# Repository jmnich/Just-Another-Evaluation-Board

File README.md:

# STM32G474QE evaluation board

Just Another Evaluation Board with as few features as possible.

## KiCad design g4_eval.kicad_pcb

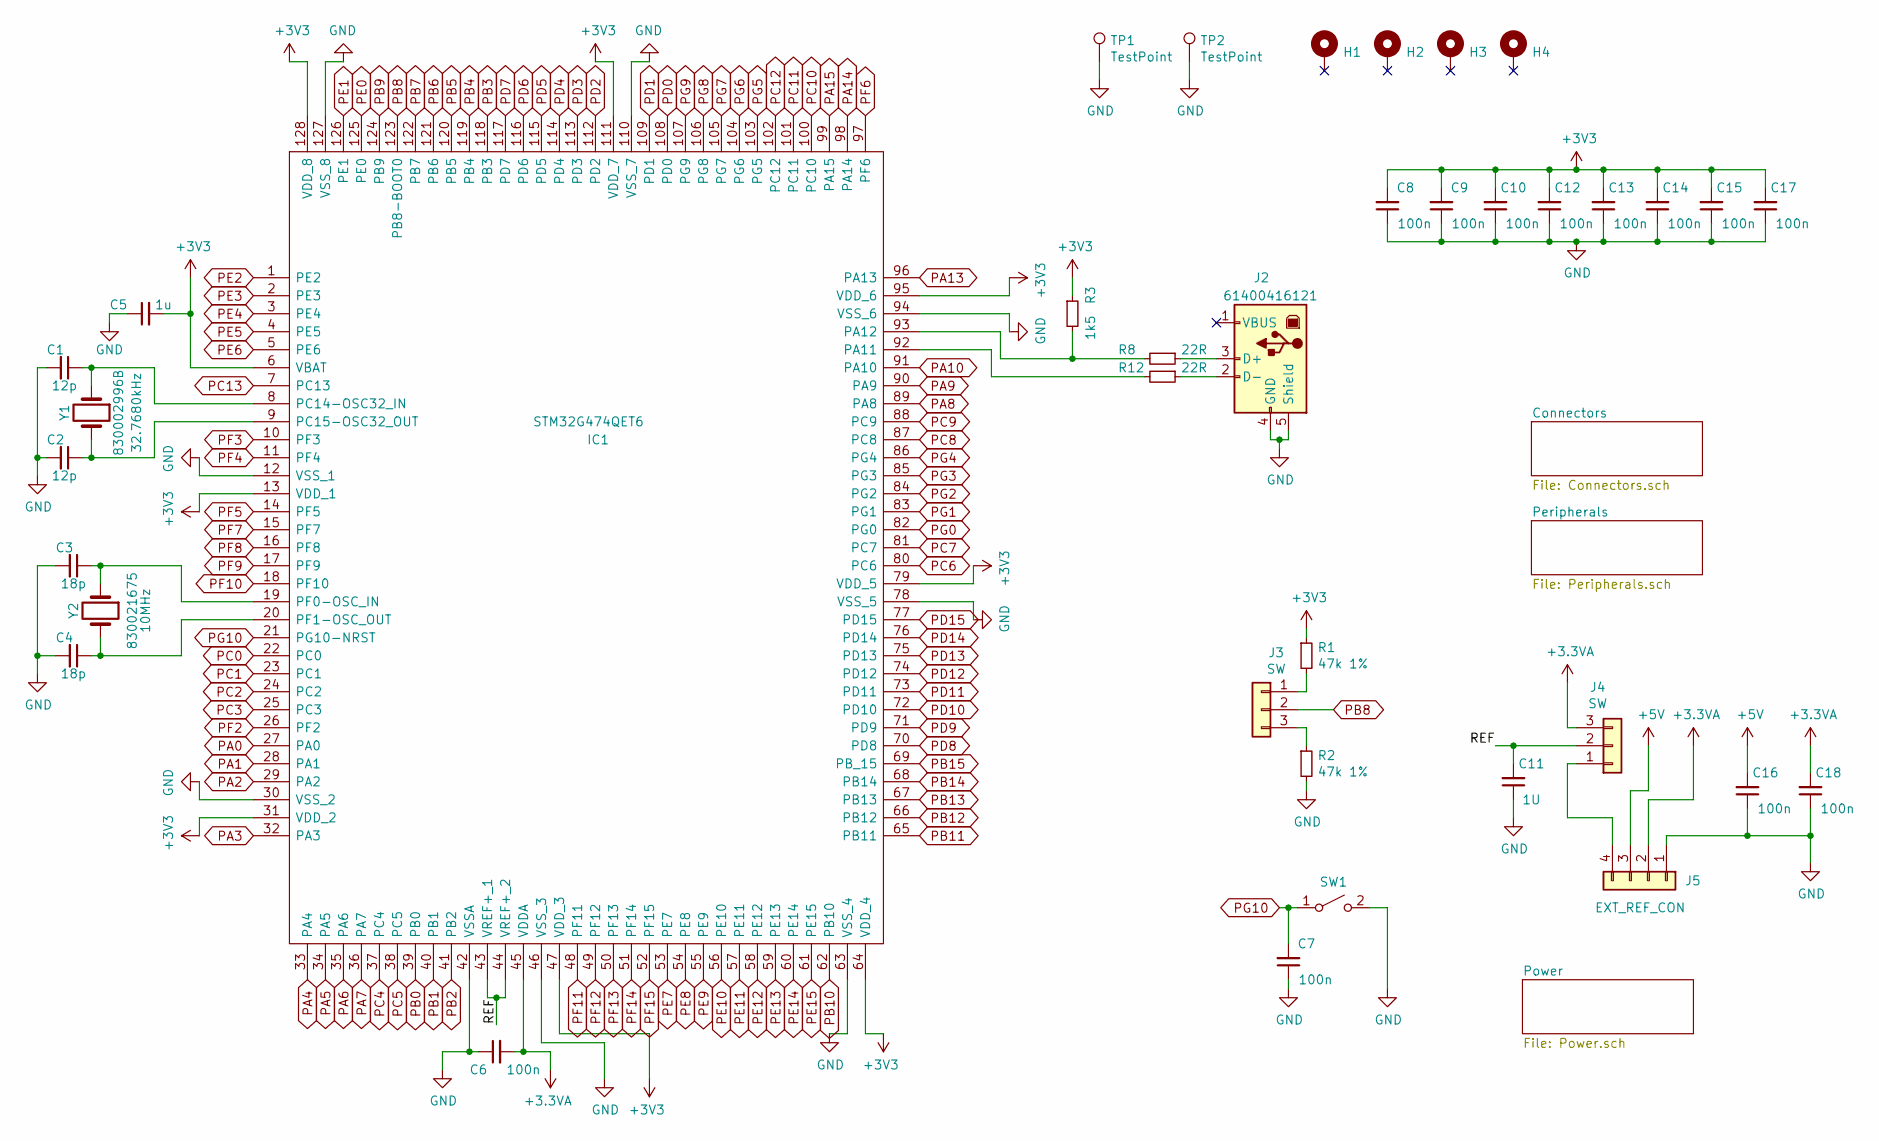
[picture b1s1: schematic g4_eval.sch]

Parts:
C1, C2: 12p; C_0603_1608Metric_Pad1.05x0.95mm_HandSolder
C3, C4: 18p; C_0603_1608Metric_Pad1.05x0.95mm_HandSolder
C5: 1u; C_0603_1608Metric_Pad1.05x0.95mm_HandSolder
C6, C7, C8, C9, C10, C12, C13, C14, C15, C16, C17, C18: 100n; C_0603_1608Metric_Pad1.05x0.95mm_HandSolder
C11: 1U; C_0603_1608Metric_Pad1.05x0.95mm_HandSolder
H1, H2, H3, H4: MountingHole_Pad; MountingHole_3.2mm_M3_Pad_Via
IC1: STM32G474QET6; LQFP-128_14x14mm_P0.4mm; Manufacturer_Part_Number STM32G474QET6; Mouser Part Number 511-STM32G474QET6
J2: 61400416121; USB_B_Horizontal
J3, J4: SW; PinHeader_1x03_P2.54mm_Vertical
J5: EXT_REF_CON; PinHeader_1x04_P2.54mm_Horizontal
R1, R2: 47k 1%; R_0603_1608Metric_Pad1.05x0.95mm_HandSolder
R3: 1k5; R_0603_1608Metric_Pad1.05x0.95mm_HandSolder
R8, R12: 22R; R_0603_1608Metric_Pad1.05x0.95mm_HandSolder
SW1: SW_SPST; SW_PUSH_6mm_H4.3mm
TP1, TP2: TestPoint; TestPoint_Loop_D2.60mm_Drill1.6mm_Beaded
Y1: 32.7680kHz; Crystal_DS10_D1.0mm_L4.3mm_Horizontal_1EP_style2; MPN 830002996B
Y2: 10MHz; Crystal_SMD_HC49-SD; MPN 830021675

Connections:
+5V: C16.2, J5.3; also elsewhere on the board
/REF: C11.2, IC1.43 (VREF+_1), IC1.44 (VREF+_2), J4.2
unnamed: C1.1, IC1.8 (PC14-OSC32_IN), Y1.1
unnamed: C2.1, IC1.9 (PC15-OSC32_OUT), Y1.2
unnamed: C3.1, IC1.19 (PF0-OSC_IN), Y2.1
unnamed: C4.1, IC1.20 (PF1-OSC_OUT), Y2.2
unnamed: IC1.92 (PA11), R12.2
unnamed: IC1.93 (PA12), R3.2, R8.2
unnamed: J3.1, R1.2
unnamed: J3.3, R2.1
unnamed: J4.1, J5.4
PA0: IC1.27 (PA0); also elsewhere on the board
PA1: IC1.28 (PA1); also elsewhere on the board
PA2: IC1.29 (PA2); also elsewhere on the board
PA3: IC1.32 (PA3); also elsewhere on the board
PA4: IC1.33 (PA4); also elsewhere on the board
PA5: IC1.34 (PA5); also elsewhere on the board
PA6: IC1.35 (PA6); also elsewhere on the board
PA7: IC1.36 (PA7); also elsewhere on the board
PA8: IC1.89 (PA8); also elsewhere on the board
PA9: IC1.90 (PA9); also elsewhere on the board
PA10: IC1.91 (PA10); also elsewhere on the board
PA15: IC1.99 (PA15); also elsewhere on the board
PB0: IC1.39 (PB0); also elsewhere on the board
PB1: IC1.40 (PB1); also elsewhere on the board
PB2: IC1.41 (PB2); also elsewhere on the board
PB3: IC1.118 (PB3); also elsewhere on the board
PB4: IC1.119 (PB4); also elsewhere on the board
PB5: IC1.120 (PB5); also elsewhere on the board
PB6: IC1.121 (PB6); also elsewhere on the board
PB7: IC1.122 (PB7); also elsewhere on the board
PB8: IC1.123 (PB8-BOOT0), J3.2; also elsewhere on the board
PB9: IC1.124 (PB9); also elsewhere on the board
PB10: IC1.62 (PB10); also elsewhere on the board
PB11: IC1.65 (PB11); also elsewhere on the board
PB12: IC1.66 (PB12); also elsewhere on the board
PB13: IC1.67 (PB13); also elsewhere on the board
PB14: IC1.68 (PB14); also elsewhere on the board
PB15: IC1.69 (PB_15); also elsewhere on the board
PC0: IC1.22 (PC0); also elsewhere on the board
PC1: IC1.23 (PC1); also elsewhere on the board
PC2: IC1.24 (PC2); also elsewhere on the board
PC3: IC1.25 (PC3); also elsewhere on the board
PC4: IC1.37 (PC4); also elsewhere on the board
PC5: IC1.38 (PC5); also elsewhere on the board
PC6: IC1.80 (PC6); also elsewhere on the board
PC7: IC1.81 (PC7); also elsewhere on the board
PC8: IC1.87 (PC8); also elsewhere on the board
PC9: IC1.88 (PC9); also elsewhere on the board
PC10: IC1.100 (PC10); also elsewhere on the board
PC11: IC1.101 (PC11); also elsewhere on the board
PC12: IC1.102 (PC12); also elsewhere on the board
PC13: IC1.7 (PC13); also elsewhere on the board
PD0: IC1.108 (PD0); also elsewhere on the board
PD1: IC1.109 (PD1); also elsewhere on the board
PD2: IC1.112 (PD2); also elsewhere on the board
PD3: IC1.113 (PD3); also elsewhere on the board
PD4: IC1.114 (PD4); also elsewhere on the board
PD5: IC1.115 (PD5); also elsewhere on the board
PD6: IC1.116 (PD6); also elsewhere on the board
PD7: IC1.117 (PD7); also elsewhere on the board
PD8: IC1.70 (PD8); also elsewhere on the board
PD9: IC1.71 (PD9); also elsewhere on the board
PD10: IC1.72 (PD10); also elsewhere on the board
PD11: IC1.73 (PD11); also elsewhere on the board
PD12: IC1.74 (PD12); also elsewhere on the board
PD13: IC1.75 (PD13); also elsewhere on the board
PD14: IC1.76 (PD14); also elsewhere on the board
PD15: IC1.77 (PD15); also elsewhere on the board
PE0: IC1.125 (PE0); also elsewhere on the board
PE1: IC1.126 (PE1); also elsewhere on the board
PE2: IC1.1 (PE2); also elsewhere on the board
PE3: IC1.2 (PE3); also elsewhere on the board
PE4: IC1.3 (PE4); also elsewhere on the board
PE5: IC1.4 (PE5); also elsewhere on the board
PE6: IC1.5 (PE6); also elsewhere on the board
PE7: IC1.53 (PE7); also elsewhere on the board
PE8: IC1.54 (PE8); also elsewhere on the board
PE9: IC1.55 (PE9); also elsewhere on the board
PE10: IC1.56 (PE10); also elsewhere on the board
PE11: IC1.57 (PE11); also elsewhere on the board
PE12: IC1.58 (PE12); also elsewhere on the board
PE13: IC1.59 (PE13); also elsewhere on the board
PE14: IC1.60 (PE14); also elsewhere on the board
PE15: IC1.61 (PE15); also elsewhere on the board
PF2: IC1.26 (PF2); also elsewhere on the board
PF3: IC1.10 (PF3); also elsewhere on the board
PF4: IC1.11 (PF4); also elsewhere on the board
PF5: IC1.14 (PF5); also elsewhere on the board
PF6: IC1.97 (PF6); also elsewhere on the board
PF7: IC1.15 (PF7); also elsewhere on the board
PF8: IC1.16 (PF8); also elsewhere on the board
PF9: IC1.17 (PF9); also elsewhere on the board
PF10: IC1.18 (PF10); also elsewhere on the board
PF11: IC1.48 (PF11); also elsewhere on the board
PF12: IC1.49 (PF12); also elsewhere on the board
PF13: IC1.50 (PF13); also elsewhere on the board
PF14: IC1.51 (PF14); also elsewhere on the board
PF15: IC1.52 (PF15); also elsewhere on the board
PG0: IC1.82 (PG0); also elsewhere on the board
PG1: IC1.83 (PG1); also elsewhere on the board
PG2: IC1.84 (PG2); also elsewhere on the board
PG3: IC1.85 (PG3); also elsewhere on the board
PG4: IC1.86 (PG4); also elsewhere on the board
PG5: IC1.103 (PG5); also elsewhere on the board
PG6: IC1.104 (PG6); also elsewhere on the board
PG7: IC1.105 (PG7); also elsewhere on the board
PG8: IC1.106 (PG8); also elsewhere on the board
PG9: IC1.107 (PG9); also elsewhere on the board
PG10: C7.2, IC1.21 (PG10-NRST), SW1.1 (A); also elsewhere on the board

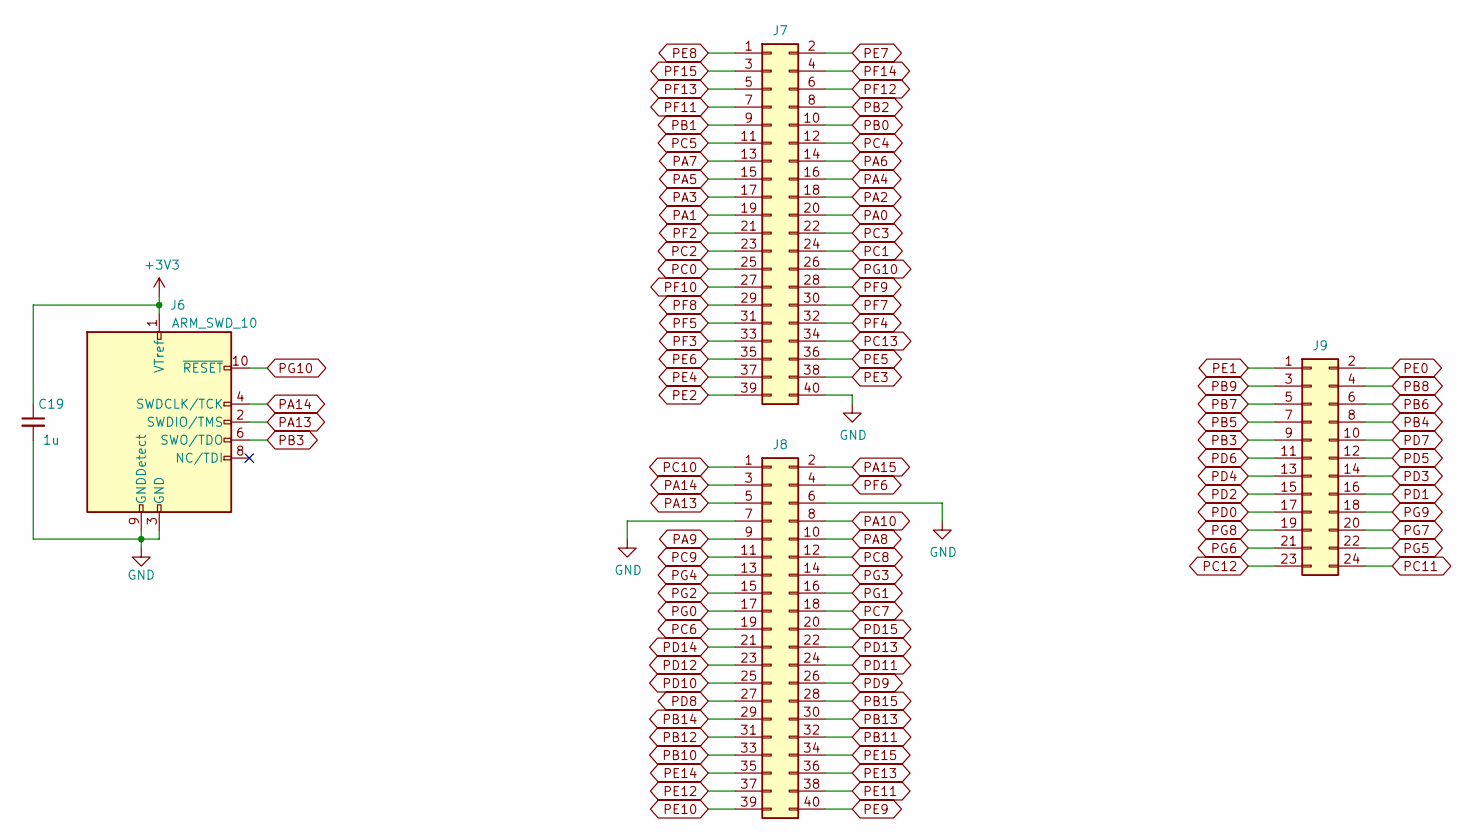
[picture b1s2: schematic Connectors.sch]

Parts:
C15: 1u; C_0603_1608Metric_Pad1.05x0.95mm_HandSolder
J2: ARM_SWD_10; JTAG_10pin_1.27_socket
J7, J8: Conn_02x20_Odd_Even; PinHeader_2x20_P2.54mm_Vertical
J9: Conn_02x12_Odd_Even; PinHeader_2x12_P2.54mm_Vertical

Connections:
PA0: J7.20; also elsewhere on the board
PA1: J7.19; also elsewhere on the board
PA2: J7.18; also elsewhere on the board
PA3: J7.17; also elsewhere on the board
PA4: J7.16; also elsewhere on the board
PA5: J7.15; also elsewhere on the board
PA6: J7.14; also elsewhere on the board
PA7: J7.13; also elsewhere on the board
PA8: J8.10; also elsewhere on the board
PA9: J8.9; also elsewhere on the board
PA10: J8.8; also elsewhere on the board
PA15: J8.2; also elsewhere on the board
PB0: J7.10; also elsewhere on the board
PB1: J7.9; also elsewhere on the board
PB2: J7.8; also elsewhere on the board
PB3: J2.6 (SWO/TDO), J9.9; also elsewhere on the board
PB4: J9.8; also elsewhere on the board
PB5: J9.7; also elsewhere on the board
PB6: J9.6; also elsewhere on the board
PB7: J9.5; also elsewhere on the board
PB8: J9.4; also elsewhere on the board
PB9: J9.3; also elsewhere on the board
PB10: J8.33; also elsewhere on the board
PB11: J8.32; also elsewhere on the board
PB12: J8.31; also elsewhere on the board
PB13: J8.30; also elsewhere on the board
PB14: J8.29; also elsewhere on the board
PB15: J8.28; also elsewhere on the board
PC0: J7.25; also elsewhere on the board
PC1: J7.24; also elsewhere on the board
PC2: J7.23; also elsewhere on the board
PC3: J7.22; also elsewhere on the board
PC4: J7.12; also elsewhere on the board
PC5: J7.11; also elsewhere on the board
PC6: J8.19; also elsewhere on the board
PC7: J8.18; also elsewhere on the board
PC8: J8.12; also elsewhere on the board
PC9: J8.11; also elsewhere on the board
PC10: J8.1; also elsewhere on the board
PC11: J9.24; also elsewhere on the board
PC12: J9.23; also elsewhere on the board
PC13: J7.34; also elsewhere on the board
PD0: J9.17; also elsewhere on the board
PD1: J9.16; also elsewhere on the board
PD2: J9.15; also elsewhere on the board
PD3: J9.14; also elsewhere on the board
PD4: J9.13; also elsewhere on the board
PD5: J9.12; also elsewhere on the board
PD6: J9.11; also elsewhere on the board
PD7: J9.10; also elsewhere on the board
PD8: J8.27; also elsewhere on the board
PD9: J8.26; also elsewhere on the board
PD10: J8.25; also elsewhere on the board
PD11: J8.24; also elsewhere on the board
PD12: J8.23; also elsewhere on the board
PD13: J8.22; also elsewhere on the board
PD14: J8.21; also elsewhere on the board
PD15: J8.20; also elsewhere on the board
PE0: J9.2; also elsewhere on the board
PE1: J9.1; also elsewhere on the board
PE2: J7.39; also elsewhere on the board
PE3: J7.38; also elsewhere on the board
PE4: J7.37; also elsewhere on the board
PE5: J7.36; also elsewhere on the board
PE6: J7.35; also elsewhere on the board
PE7: J7.2; also elsewhere on the board
PE8: J7.1; also elsewhere on the board
PE9: J8.40; also elsewhere on the board
PE10: J8.39; also elsewhere on the board
PE11: J8.38; also elsewhere on the board
PE12: J8.37; also elsewhere on the board
PE13: J8.36; also elsewhere on the board
PE14: J8.35; also elsewhere on the board
PE15: J8.34; also elsewhere on the board
PF2: J7.21; also elsewhere on the board
PF3: J7.33; also elsewhere on the board
PF4: J7.32; also elsewhere on the board
PF5: J7.31; also elsewhere on the board
PF6: J8.4; also elsewhere on the board
PF7: J7.30; also elsewhere on the board
PF8: J7.29; also elsewhere on the board
PF9: J7.28; also elsewhere on the board
PF10: J7.27; also elsewhere on the board
PF11: J7.7; also elsewhere on the board
PF12: J7.6; also elsewhere on the board
PF13: J7.5; also elsewhere on the board
PF14: J7.4; also elsewhere on the board
PF15: J7.3; also elsewhere on the board
PG0: J8.17; also elsewhere on the board
PG1: J8.16; also elsewhere on the board
PG2: J8.15; also elsewhere on the board
PG3: J8.14; also elsewhere on the board
PG4: J8.13; also elsewhere on the board
PG5: J9.22; also elsewhere on the board
PG6: J9.21; also elsewhere on the board
PG7: J9.20; also elsewhere on the board
PG8: J9.19; also elsewhere on the board
PG9: J9.18; also elsewhere on the board
PG10: J2.10 (~RESET~), J7.26; also elsewhere on the board

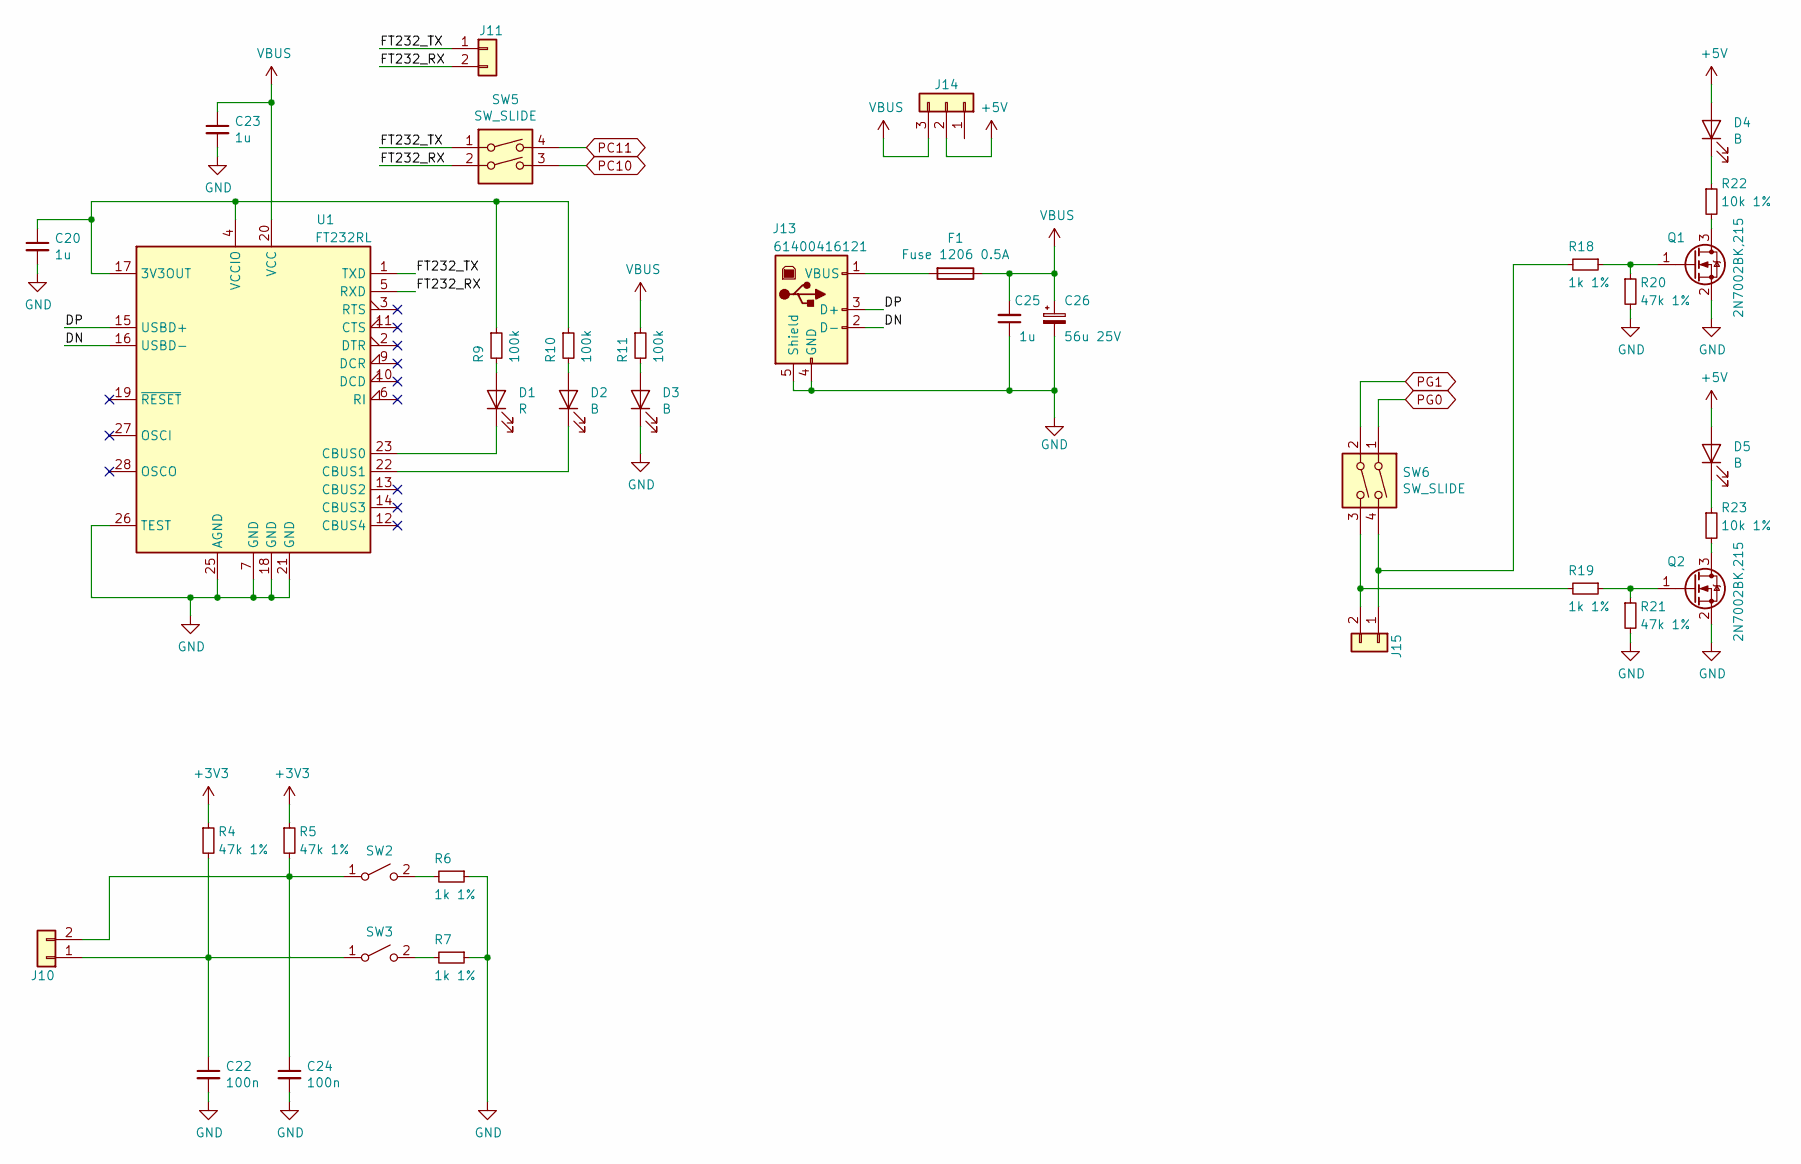
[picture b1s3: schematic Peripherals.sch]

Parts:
C20, C23, C25: 1u; C_0603_1608Metric_Pad1.05x0.95mm_HandSolder
C22, C24: 100n; C_0603_1608Metric_Pad1.05x0.95mm_HandSolder
C26: 56u 25V; CP_Elec_6.3x5.9
D1: R; LED_0603_1608Metric_Pad1.05x0.95mm_HandSolder
D2, D3, D4, D5: B; LED_0603_1608Metric_Pad1.05x0.95mm_HandSolder
F1: Fuse 1206 0.5A; Fuse_1206_3216Metric_Pad1.42x1.75mm_HandSolder
J10, J11, J15: Conn_01x02; PinHeader_1x02_P2.54mm_Vertical
J13: 61400416121; USB_B_Horizontal
J14: Conn_01x03; PinHeader_1x03_P2.54mm_Vertical
Q1, Q2: 2N7002BK,215; SOT-23
R4, R5, R20, R21: 47k 1%; R_0603_1608Metric_Pad1.05x0.95mm_HandSolder
R6, R7, R18, R19: 1k 1%; R_0603_1608Metric_Pad1.05x0.95mm_HandSolder
R9, R10, R11: 100k; R_0603_1608Metric_Pad1.05x0.95mm_HandSolder
R22, R23: 10k 1%; R_0603_1608Metric_Pad1.05x0.95mm_HandSolder
SW2, SW3: SW_SPST; SW_PUSH_6mm_H4.3mm
SW5, SW6: SW_SLIDE; SW_DIP_SPSTx02_Slide_9.78x7.26mm_W7.62mm_P2.54mm
U1: FT232RL; SSOP-28_5.3x10.2mm_P0.65mm

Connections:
+5V: D4.2 (A), D5.2 (A), J14.2; also elsewhere on the board
/Peripherals/DN: J13.2 (D-), U1.16 (USBD-)
/Peripherals/DP: J13.3 (D+), U1.15 (USBD+)
/Peripherals/FT232_RX: J11.2, SW5.2, U1.5 (RXD)
/Peripherals/FT232_TX: J11.1, SW5.1, U1.1 (TXD)
unnamed: C20.1, R9.1, R10.1, U1.4 (VCCIO), U1.17 (3V3OUT)
unnamed: C22.1, J10.1, R4.2, SW3.1 (A)
unnamed: C24.1, J10.2, R5.2, SW2.1 (A)
unnamed: D1.1 (K), U1.23 (CBUS0)
unnamed: D1.2 (A), R9.2
unnamed: D2.1 (K), U1.22 (CBUS1)
unnamed: D2.2 (A), R10.2
unnamed: D3.2 (A), R11.2
unnamed: D4.1 (K), R22.1
unnamed: D5.1 (K), R23.1
unnamed: F1.2, J13.1 (VBUS)
unnamed: J15.1, R18.2, SW6.4
unnamed: J15.2, R19.2, SW6.3
unnamed: Q1.1 (G), R18.1, R20.1
unnamed: Q1.3 (D), R22.2
unnamed: Q2.1 (G), R19.1, R21.1
unnamed: Q2.3 (D), R23.2
unnamed: R6.2, SW2.2 (B)
unnamed: R7.2, SW3.2 (B)
PC10: SW5.3; also elsewhere on the board
PC11: SW5.4; also elsewhere on the board
PG0: SW6.1; also elsewhere on the board
PG1: SW6.2; also elsewhere on the board
VBUS: C23.1, C25.2, C26.1, F1.1, J14.3, R11.1, U1.20 (VCC)

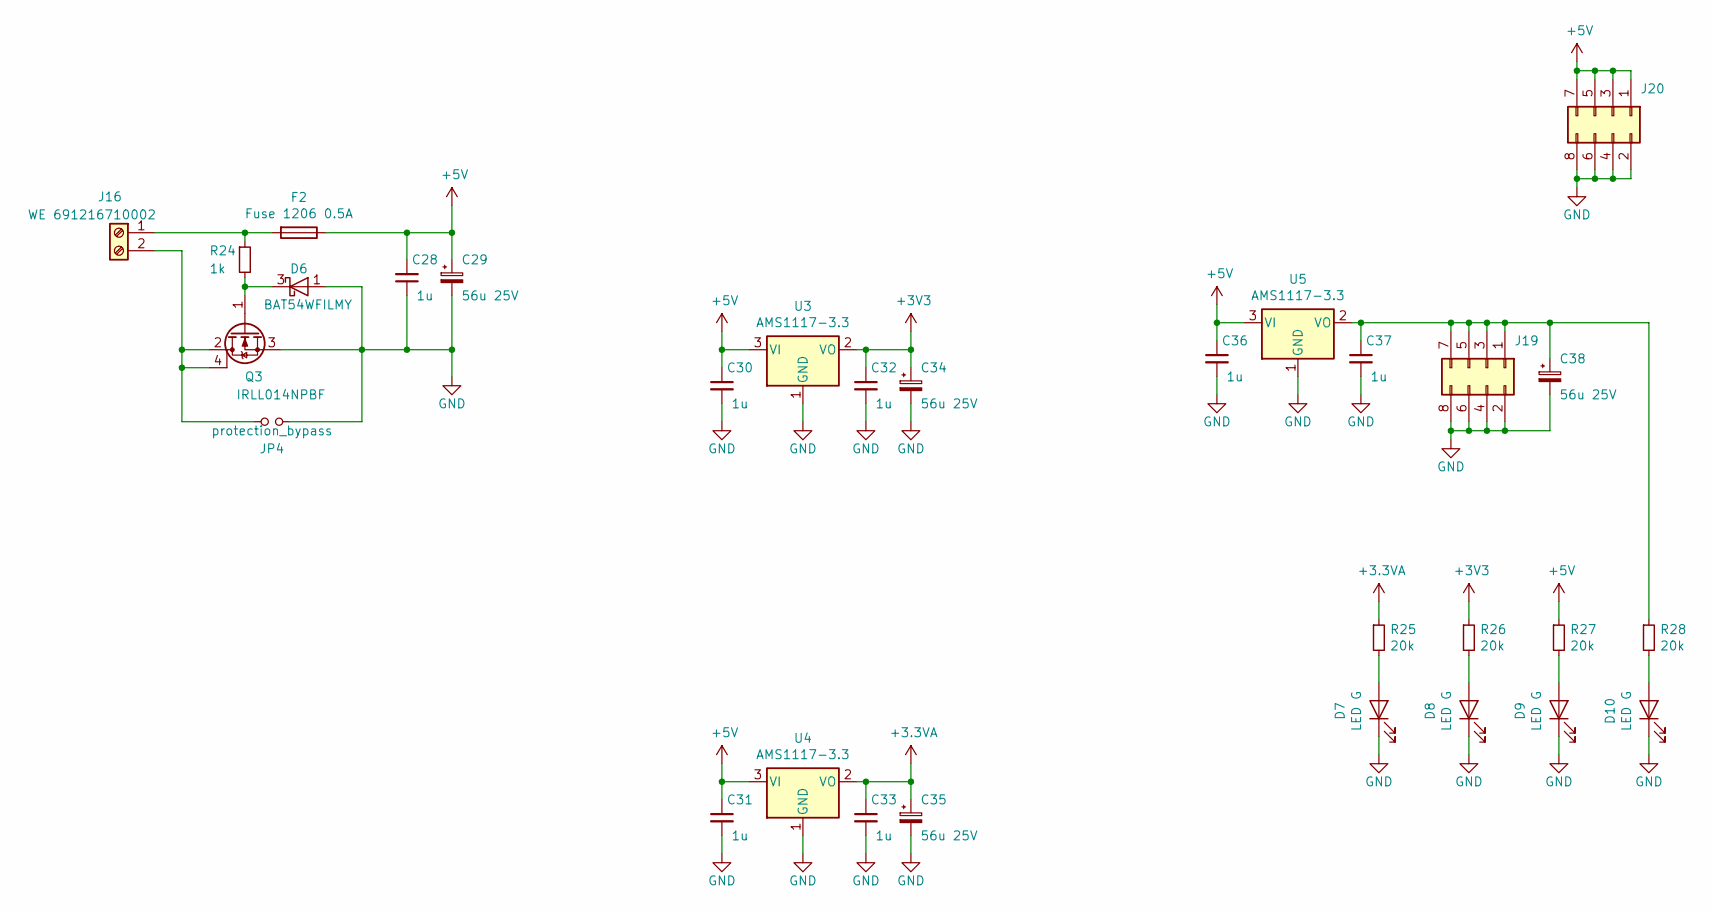
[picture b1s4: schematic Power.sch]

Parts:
C28, C30, C31, C32, C33, C36, C37: 1u; C_0603_1608Metric_Pad1.05x0.95mm_HandSolder
C29, C34, C35, C38: 56u 25V; CP_Elec_6.3x5.9
D6: BAT54WFILMY; SOT-323_SC-70
D7, D8, D9, D10: LED G; LED_0603_1608Metric_Pad1.05x0.95mm_HandSolder
F2: Fuse 1206 0.5A; Fuse_1206_3216Metric_Pad1.42x1.75mm_HandSolder
J16: WE 691216710002; Terminal_block_WE691216710002
J19, J20: Conn_02x04_Odd_Even; PinHeader_2x04_P2.54mm_Vertical
JP4: protection_bypass; R_0805_2012Metric_Pad1.15x1.40mm_HandSolder
Q3: IRLL014NPBF; SOT-223
R24: 1k; R_0603_1608Metric_Pad1.05x0.95mm_HandSolder
R25, R26, R27, R28: 20k; R_0603_1608Metric_Pad1.05x0.95mm_HandSolder
U3, U4, U5: AMS1117-3.3; SOT-223-3_TabPin2

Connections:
+5V: C28.2, C29.1, C30.1, C31.1, C36.1, F2.1, J20.1, J20.3, J20.5, J20.7, R27.1, U3.3 (VI), U4.3 (VI), U5.3 (VI); also elsewhere on the board
unnamed: C37.1, C38.1, J19.1, J19.3, J19.5, J19.7, R28.1, U5.2 (VO)
unnamed: D6.3 (K), Q3.1 (G), R24.2
unnamed: D7.2 (A), R25.2
unnamed: D8.2 (A), R26.2
unnamed: D9.2 (A), R27.2
unnamed: D10.2 (A), R28.2
unnamed: F2.2, J16.1, R24.1
unnamed: J16.2, JP4.1, Q3.2 (D), Q3.4 (D)

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
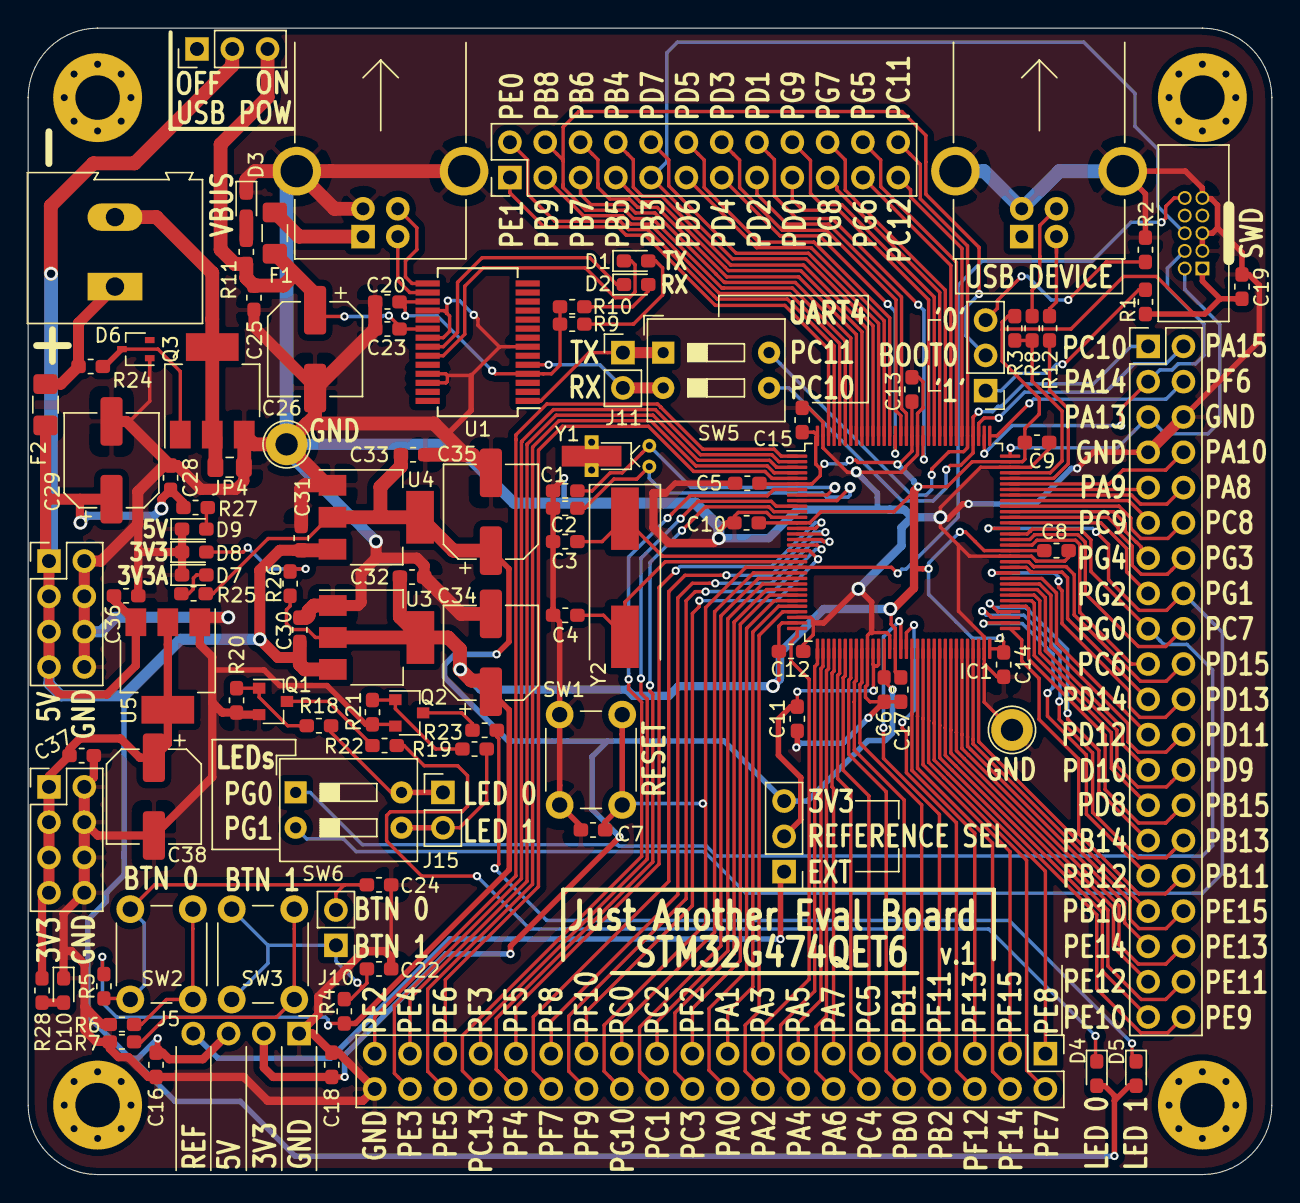
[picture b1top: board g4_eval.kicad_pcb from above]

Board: 2 copper layers, 89.5 x 82.5 mm, 109 parts (0 on the bottom side), 149 nets.

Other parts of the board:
C19: 1u; C_0603_1608Metric_Pad1.05x0.95mm_HandSolder
J6: ARM_SWD_10; JTAG_10pin_1.27_socket

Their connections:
PB3: J6.6; also elsewhere on the board
PG10: J6.10; also elsewhere on the board

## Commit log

2021-02-28 readme and image
2021-02-28 Production files generated
